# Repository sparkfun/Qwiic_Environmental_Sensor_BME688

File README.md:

SparkFun Environmental Sensor - BME688 (Qwiic)
========================================

[*SparkFun Environmental Sensor - BME688 (Qwiic) (SEN-19096)*](https://www.sparkfun.com/products/19096)

The SparkFun Environmental Sensor - BME688 (Qwiic) is a breakout board that combines a gas scanning sensor with temperature, humidity, and barometric pressure sensing for a complete environmental sensor in a single package. The gas sensor on the BME688 can detect a wide variety of volatile organic compounds (VOCs), volatile sulfur compounds (VSCs), and other gases such as carbon monoxide and hydrogen in the part per billion (ppb) range. Combine that with precise temperature, humidity, and barometric pressure and the BME688 can work as a completely standalone environmental sensor all in a 1in. x 1in. breakout!

The sensor communicates via either I2C or SPI. We've broken out the I2C pins to our Qwiic system so no soldering is required to connect it to the rest of your system but if you would prefer, both the I2C and SPI pins are also broken out to standard 0.1in.-spaced pins.

**Note:** While this sensor can be used with the BME AI-Studio and BSEC2 Arduino library; it is recommended for the AI functionality, users purchase the BME688 Evaluation Board (Coming Soon) for ease of use.

<p><div class="alert alert-warning"><b>Important:</b> In order to avoid contamination of its gas scanning capabilities, DO NOT touch the metallic casing of the BME688 sensor. Please, handle with care.</div></p>

_The SparkFun [Qwiic connect system](https://www.sparkfun.com/qwiic) is an ecosystem of I2C sensors, actuators, shields and cables that make prototyping faster and less prone to error. All Qwiic-enabled boards use a common 1mm pitch, 4-pin JST connector. This reduces the amount of required PCB space, and polarized connections mean you can’t hook it up wrong._

Repository Contents
-------------------

* **/Test Sketches** - Engineer's Arduino example code
* **/Hardware** - Eagle design files (.brd, .sch)
* **/Hardware/Production** - Production panel files (.brd)

Documentation
--------------

* **[Datasheet](https://www.bosch-sensortec.com/media/boschsensortec/downloads/datasheets/bst-bme688-ds000.pdf)** - BME688 Datasheet
* **[Hookup Guide](https://learn.sparkfun.com/tutorials/1168)** - SparkFun Environmental Sensor Breakout - BME68x (Qwiic) Hookup Guide
* **Arduino Libraries:**
    * **[BME680 Arduino Library](https://github.com/SV-Zanshin/BME680)** - Arduino Library used in Hookup Guide
    * **[BME68x Arduino Library](https://github.com/BoschSensortec/Bosch-BME68x-Library)** - Bosch's Arduino Library for BME68x Sensors
    * **[BSEC2 Arduino Library](https://github.com/BoschSensortec/Bosch-BSEC2-Library)** - Bosch's Arduino Library for BME AI-Studio
* **BME AI Studio:**
    * **BME AI-Studio (Mac/Windows)** *(Download from [Bosch software page](https://www.bosch-sensortec.com/software-tools/software/bme688-software/))*
    * **[BME AI-Studio Manual](https://www.bosch-sensortec.com/media/boschsensortec/downloads/application_notes_1/bst-bme688-an001.pdf)** - User Manual for BME AI-Studio

Product Versions
----------------
* [SEN-19096](https://www.sparkfun.com/products/19096) -  initial release

License Information
-------------------

This product is _**open source**_! 

Please review the LICENSE.md file for license information. 

If you have any questions or concerns on licensing, please contact technical support on our [SparkFun forums](https://forum.sparkfun.com/viewforum.php?f=152).

Distributed as-is; no warranty is given.

- Your friends at SparkFun.

_<COLLABORATION CREDIT>_

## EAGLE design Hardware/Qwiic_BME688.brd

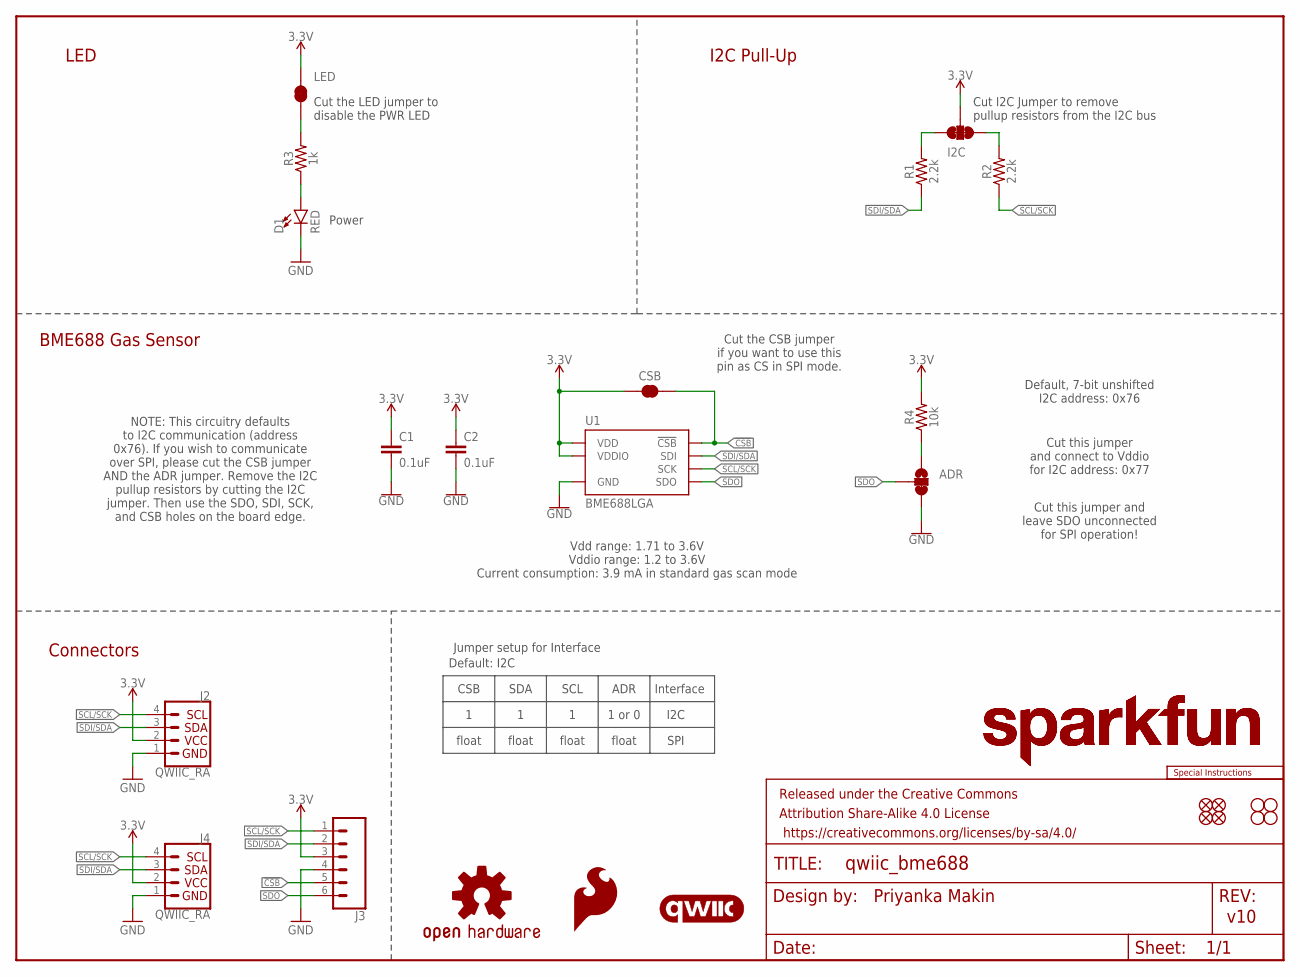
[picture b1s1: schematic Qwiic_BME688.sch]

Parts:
ADR: JUMPER-SMT_3_1-NC_TRACE_SILK; SMT-JUMPER_3_1-NC_TRACE_SILK
C1, C2: 0.1uF; 0603
CSB: JUMPER-SMT_2_NC_TRACE_SILK; SMT-JUMPER_2_NC_TRACE_SILK
D1: RED; LED-0603
FRAME1: FRAME-LETTER; CREATIVE_COMMONS
I2C: JUMPER-SMT_3_2-NC_TRACE_SILK; SMT-JUMPER_3_2-NC_TRACE_SILK
J2, J4: QWIIC_RA; JST04_1MM_RA
J3: CONN_06NO_SILK_NO_POP; 1X06_NO_SILK
JP1, JP2, JP5, JP6: FIDUCIALUFIDUCIAL; FIDUCIAL-MICRO
JP3, JP4, JP7, JP8: STAND-OFF
LED: JUMPER-SMT_2_NC_TRACE_SILK; SMT-JUMPER_2_NC_TRACE_SILK
LOGO1: SPECIAL_INSTRUCTIONS-ORDERING; ORDERING_INSTRUCTIONS
LOGO2: QWIIC_LOGO_5MM; QWIIC_5MM
LOGO3, LOGO6: SFE_LOGO_NAME.1_INCH; SFE_LOGO_NAME_.1
LOGO4: SFE_LOGO_FLAME.1_INCH; SFE_LOGO_FLAME_.1
LOGO5: OSHW-LOGOS; OSHW-LOGO-S
R1, R2: 2.2k; 0603
R3: 1k; 0603
R4: 10k; 0603
U1: BME688LGA; LGA_8PIN

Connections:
3.3V: C1.1, C2.1, CSB.1, I2C.2, J2.2, J3.3, J4.2, LED.2, R4.2, U1.6 (VDDIO), U1.8 (VDD)
!CSB!: CSB.2, J3.5, U1.2 (!CSB!)
GND: ADR.3, C1.2, C2.2, D1.C, J2.1, J3.4, J4.1, U1.1 (GND), U1.7 (GND)
unnamed: LED.1, R3.2
unnamed: I2C.3, R1.2
unnamed: D1.A, R3.1
unnamed: I2C.1, R2.2
unnamed: ADR.1, R4.1
SCL/SCK: J2.4, J3.1, J4.4, R2.1, U1.4 (SCK)
SDI/SDA: J2.3, J3.2, J4.3, R1.1, U1.3 (SDI)
SDO: ADR.2, J3.6, U1.5 (SDO)

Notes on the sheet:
v10
Default, 7-bit unshifted I2C address: 0x76
Power
I2C Pull-Up
BME688 Gas Sensor
Connectors
Cut the LED jumper to disable the PWR LED
Cut I2C Jumper to remove pullup resistors from the I2C bus
LED
Priyanka Makin
Vdd range: 1.71 to 3.6V Vddio range: 1.2 to 3.6V Current consumption: 3.9 mA in standard gas scan mode
Cut this jumper and connect to Vddio for I2C address: 0x77
Cut this jumper and leave SDO unconnected for SPI operation!
Cut the CSB jumper if you want to use this pin as CS in SPI mode.
NOTE: This circuitry defaults to I2C communication (address 0x76). If you wish to communicate over SPI, please cut the CSB jumper AND the ADR jumper. Remove the I2C pullup resistors by cutting the I2C jumper. Then use the SDO, SDI, SCK, and CSB holes on the board edge.
SCL
CSB
ADR
1 or 0
float
Interface
I2C
SPI
SDA
Jumper setup for Interface
Default: I2C

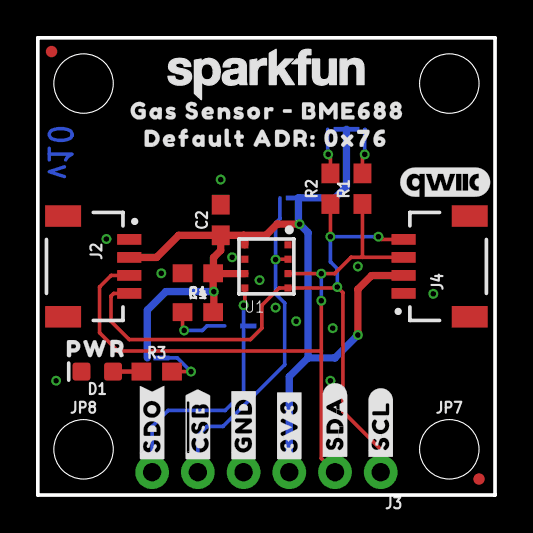
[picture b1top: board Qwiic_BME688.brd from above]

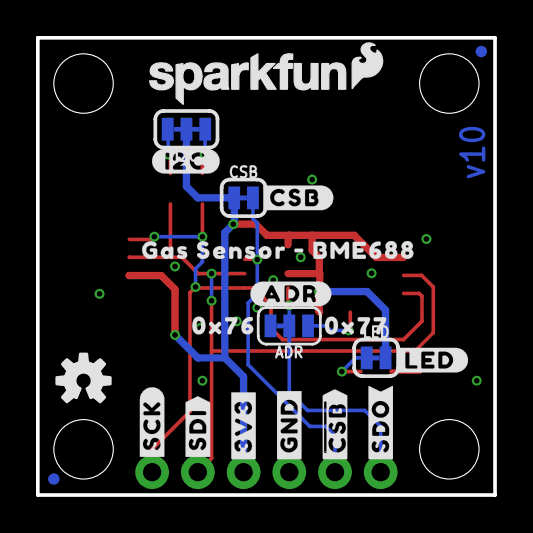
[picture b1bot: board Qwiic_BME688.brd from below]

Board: 2 copper layers, 25.4 x 25.4 mm, 52 parts (22 on the bottom side), 11 nets.

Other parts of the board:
U$1, U$33: #GND#0
U$2, U$16: #SDO#0
U$3: #CSB#0
U$5: PWR0
U$6: #I2C#0
U$7, U$10: GAS_SENSOR_#_BME6880
U$8: #LED#0
U$9: 0X760
U$11: #ADR#0
U$12: DEFAULT_ADR#_0X760
U$13: 0X770
U$14, U$15: #3V3#0
U$19: #SDI#0
U$20: #SCK#0
U$21, U$22: ##CSB##0
U$35: #SDA#0
U$36: #SCL#0

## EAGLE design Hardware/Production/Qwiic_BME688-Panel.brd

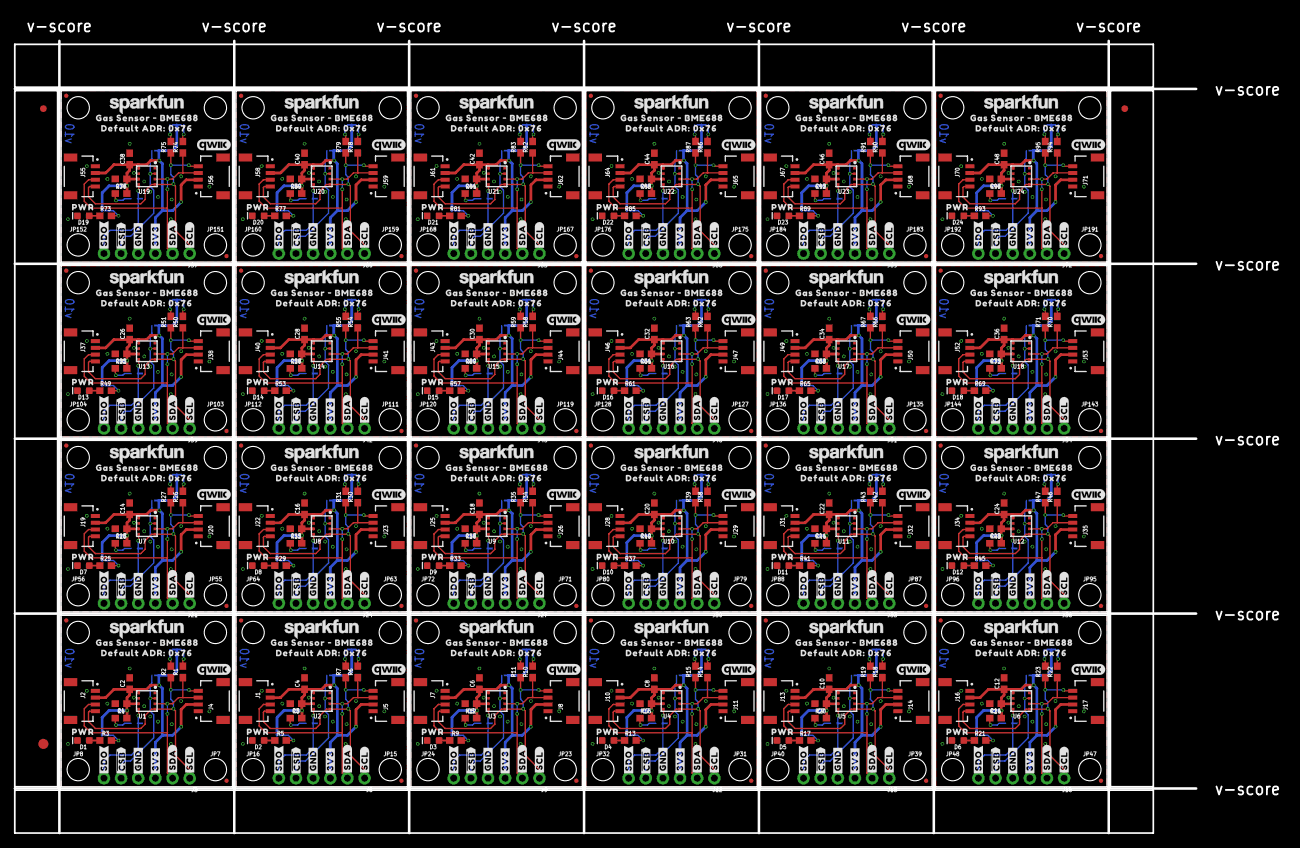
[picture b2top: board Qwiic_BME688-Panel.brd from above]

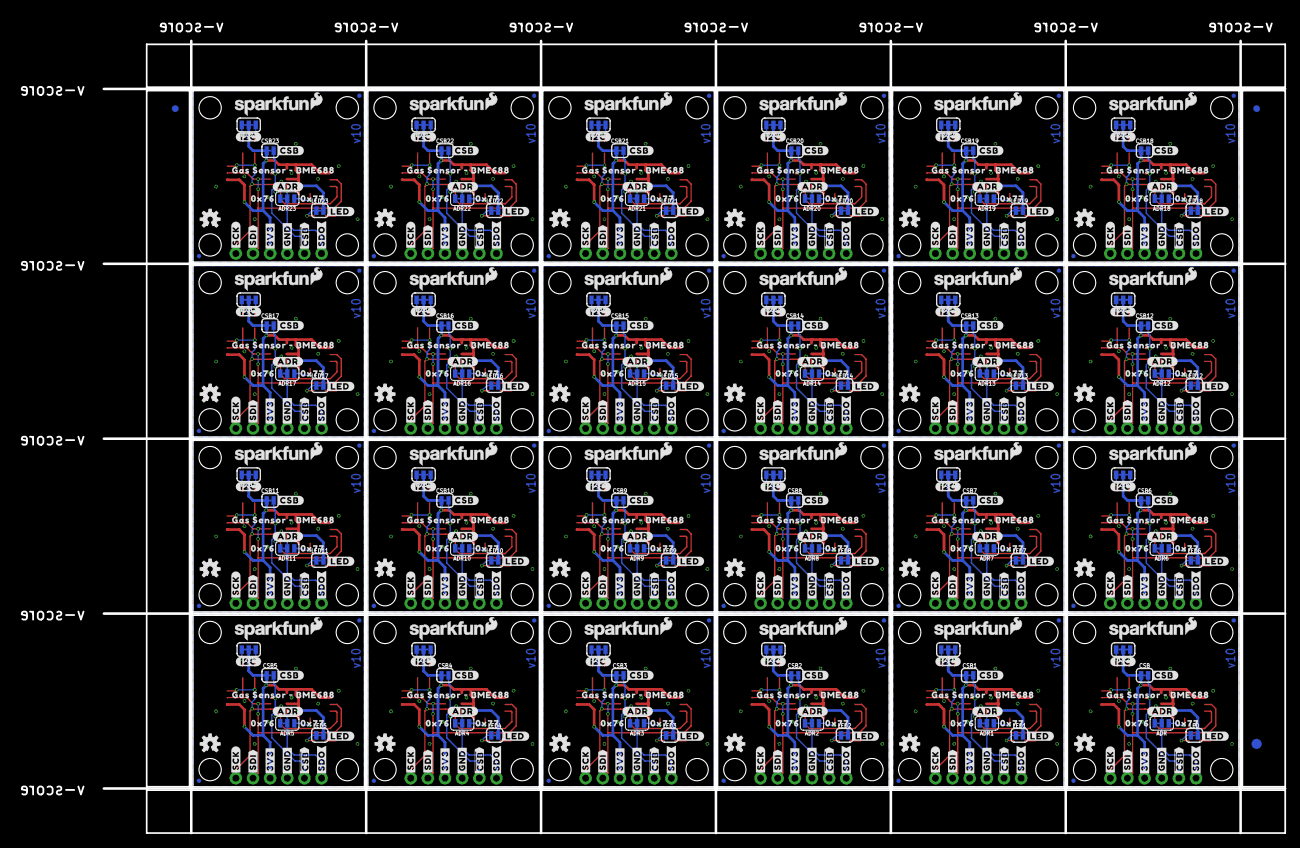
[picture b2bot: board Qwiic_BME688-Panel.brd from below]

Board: 2 copper layers, 188.2 x 121.2 mm, 1206 parts (531 on the bottom side), 264 nets.

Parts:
ADR, ADR1, ADR2, ADR3, ADR4, ADR5, ADR6, ADR7, ADR8, ADR9, ADR10, ADR11, ADR12, ADR13, ADR14, ADR15, ADR16, ADR17, ADR18, ADR19, ADR20, ADR21, ADR22, ADR23: JUMPER-SMT_3_1-NC_TRACE_SILK; SMT-JUMPER_3_1-NC_TRACE_SILK
C1, C2, C3, C4, C5, C6, C7, C8, C9, C10, C11, C12, C13, C14, C15, C16, C17, C18, C19, C20, C21, C22, C23, C24, C25, C26, C27, C28, C29, C30, C31, C32, C33, C34, C35, C36, C37, C38, C39, C40, C41, C42, C43, C44, C45, C46, C47, C48: 0.1uF; 0603
CSB, CSB1, CSB2, CSB3, CSB4, CSB5, CSB6, CSB7, CSB8, CSB9, CSB10, CSB11, CSB12, CSB13, CSB14, CSB15, CSB16, CSB17, CSB18, CSB19, CSB20, CSB21, CSB22, CSB23: JUMPER-SMT_2_NC_TRACE_SILK; SMT-JUMPER_2_NC_TRACE_SILK
D1, D2, D3, D4, D5, D6, D7, D8, D9, D10, D11, D12, D13, D14, D15, D16, D17, D18, D19, D20, D21, D22, D23, D24: RED; LED-0603
E$1, E$2, E$3, E$4: FIDUCIAL-1X2
E$5, E$6: FIDUCIAL-1.5X3
I2C, I2C1, I2C2, I2C3, I2C4, I2C5, I2C6, I2C7, I2C8, I2C9, I2C10, I2C11, I2C12, I2C13, I2C14, I2C15, I2C16, I2C17, I2C18, I2C19, I2C20, I2C21, I2C22, I2C23: JUMPER-SMT_3_2-NC_TRACE_SILK; SMT-JUMPER_3_2-NC_TRACE_SILK
J1, J2, J4, J5, J7, J8, J10, J11, J13, J14, J16, J17, J19, J20, J22, J23, J25, J26, J28, J29, J31, J32, J34, J35, J37, J38, J40, J41, J43, J44, J46, J47, J49, J50, J52, J53, J55, J56, J58, J59, J61, J62, J64, J65, J67, J68, J70, J71: QWIIC_RA; JST04_1MM_RA
J3, J6, J9, J12, J15, J18, J21, J24, J27, J30, J33, J36, J39, J42, J45, J48, J51, J54, J57, J60, J63, J66, J69, J72: 1X06_NO_SILK
JP1, JP2, JP5, JP6, JP11, JP12, JP13, JP14, JP19, JP20, JP21, JP22, JP27, JP28, JP29, JP30, JP35, JP36, JP37, JP38, JP43, JP44, JP45, JP46, JP51, JP52, JP53, JP54, JP59, JP60, JP61, JP62, JP67, JP68, JP69, JP70, JP75, JP76, JP77, JP78, JP83, JP84, JP85, JP86, JP91, JP92, JP93, JP94, JP99, JP100, JP101, JP102, JP107, JP108, JP109, JP110, JP115, JP116, JP117, JP118, JP123, JP124, JP125, JP126, JP131, JP132, JP133, JP134, JP139, JP140, JP141, JP142, JP147, JP148, JP149, JP150, JP155, JP156, JP157, JP158, JP163, JP164, JP165, JP166, JP171, JP172, JP173, JP174, JP179, JP180, JP181, JP182, JP187, JP188, JP189, JP190: FIDUCIALUFIDUCIAL; FIDUCIAL-MICRO
JP3, JP4, JP7, JP8, JP9, JP10, JP15, JP16, JP17, JP18, JP23, JP24, JP25, JP26, JP31, JP32, JP33, JP34, JP39, JP40, JP41, JP42, JP47, JP48, JP49, JP50, JP55, JP56, JP57, JP58, JP63, JP64, JP65, JP66, JP71, JP72, JP73, JP74, JP79, JP80, JP81, JP82, JP87, JP88, JP89, JP90, JP95, JP96, JP97, JP98, JP103, JP104, JP105, JP106, JP111, JP112, JP113, JP114, JP119, JP120, JP121, JP122, JP127, JP128, JP129, JP130, JP135, JP136, JP137, JP138, JP143, JP144, JP145, JP146, JP151, JP152, JP153, JP154, JP159, JP160, JP161, JP162, JP167, JP168, JP169, JP170, JP175, JP176, JP177, JP178, JP183, JP184, JP185, JP186, JP191, JP192: STAND-OFF
LED, LED1, LED2, LED3, LED4, LED5, LED6, LED7, LED8, LED9, LED10, LED11, LED12, LED13, LED14, LED15, LED16, LED17, LED18, LED19, LED20, LED21, LED22, LED23: JUMPER-SMT_2_NC_TRACE_SILK; SMT-JUMPER_2_NC_TRACE_SILK
LOGO1, LOGO5, LOGO11, LOGO16, LOGO21, LOGO26, LOGO31, LOGO36, LOGO41, LOGO46, LOGO51, LOGO56, LOGO61, LOGO66, LOGO71, LOGO76, LOGO81, LOGO86, LOGO91, LOGO96, LOGO101, LOGO106, LOGO111, LOGO116: OSHW-LOGOS; OSHW-LOGO-S
LOGO2, LOGO7, LOGO12, LOGO17, LOGO22, LOGO27, LOGO32, LOGO37, LOGO42, LOGO47, LOGO52, LOGO57, LOGO62, LOGO67, LOGO72, LOGO77, LOGO82, LOGO87, LOGO92, LOGO97, LOGO102, LOGO107, LOGO112, LOGO117: QWIIC_LOGO_5MM; QWIIC_5MM
LOGO3, LOGO6, LOGO8, LOGO10, LOGO13, LOGO15, LOGO18, LOGO20, LOGO23, LOGO25, LOGO28, LOGO30, LOGO33, LOGO35, LOGO38, LOGO40, LOGO43, LOGO45, LOGO48, LOGO50, LOGO53, LOGO55, LOGO58, LOGO60, LOGO63, LOGO65, LOGO68, LOGO70, LOGO73, LOGO75, LOGO78, LOGO80, LOGO83, LOGO85, LOGO88, LOGO90, LOGO93, LOGO95, LOGO98, LOGO100, LOGO103, LOGO105, LOGO108, LOGO110, LOGO113, LOGO115, LOGO118, LOGO120: SFE_LOGO_NAME.1_INCH; SFE_LOGO_NAME_.1
LOGO4, LOGO9, LOGO14, LOGO19, LOGO24, LOGO29, LOGO34, LOGO39, LOGO44, LOGO49, LOGO54, LOGO59, LOGO64, LOGO69, LOGO74, LOGO79, LOGO84, LOGO89, LOGO94, LOGO99, LOGO104, LOGO109, LOGO114, LOGO119: SFE_LOGO_FLAME.1_INCH; SFE_LOGO_FLAME_.1
R1, R2, R6, R7, R10, R11, R14, R15, R18, R19, R22, R23, R26, R27, R30, R31, R34, R35, R38, R39, R42, R43, R46, R47, R50, R51, R54, R55, R58, R59, R62, R63, R66, R67, R70, R71, R74, R75, R78, R79, R82, R83, R86, R87, R90, R91, R94, R95: 2.2k; 0603
R3, R5, R9, R13, R17, R21, R25, R29, R33, R37, R41, R45, R49, R53, R57, R61, R65, R69, R73, R77, R81, R85, R89, R93: 1k; 0603
R4, R8, R12, R16, R20, R24, R28, R32, R36, R40, R44, R48, R52, R56, R60, R64, R68, R72, R76, R80, R84, R88, R92, R96: 10k; 0603
U1, U2, U3, U4, U5, U6, U7, U8, U9, U10, U11, U12, U13, U14, U15, U16, U17, U18, U19, U20, U21, U22, U23, U24: BME688LGA; LGA_8PIN
U$1, U$4, U$23, U$33, U$45, U$48, U$67, U$70, U$89, U$92, U$111, U$114, U$133, U$136, U$155, U$158, U$177, U$180, U$199, U$202, U$221, U$224, U$243, U$246, U$265, U$268, U$287, U$290, U$309, U$312, U$331, U$334, U$353, U$356, U$375, U$378, U$397, U$400, U$419, U$422, U$441, U$444, U$463, U$466, U$485, U$488, U$507, U$510: #GND#0
U$2, U$16, U$38, U$39, U$60, U$61, U$82, U$83, U$104, U$105, U$126, U$127, U$148, U$149, U$170, U$171, U$192, U$193, U$214, U$215, U$236, U$237, U$258, U$259, U$280, U$281, U$302, U$303, U$324, U$325, U$346, U$347, U$368, U$369, U$390, U$391, U$412, U$413, U$434, U$435, U$456, U$457, U$478, U$479, U$500, U$501, U$522, U$523: #SDO#0
U$3, U$42, U$64, U$86, U$108, U$130, U$152, U$174, U$196, U$218, U$240, U$262, U$284, U$306, U$328, U$350, U$372, U$394, U$416, U$438, U$460, U$482, U$504, U$526: #CSB#0
U$5, U$24, U$49, U$71, U$93, U$115, U$137, U$159, U$181, U$203, U$225, U$247, U$269, U$291, U$313, U$335, U$357, U$379, U$401, U$423, U$445, U$467, U$489, U$511: PWR0
U$6, U$29, U$54, U$76, U$98, U$120, U$142, U$164, U$186, U$208, U$230, U$252, U$274, U$296, U$318, U$340, U$362, U$384, U$406, U$428, U$450, U$472, U$494, U$516: #I2C#0
U$7, U$10, U$25, U$27, U$50, U$52, U$72, U$74, U$94, U$96, U$116, U$118, U$138, U$140, U$160, U$162, U$182, U$184, U$204, U$206, U$226, U$228, U$248, U$250, U$270, U$272, U$292, U$294, U$314, U$316, U$336, U$338, U$358, U$360, U$380, U$382, U$402, U$404, U$424, U$426, U$446, U$448, U$468, U$470, U$490, U$492, U$512, U$514: GAS_SENSOR_#_BME6880
U$8, U$28, U$53, U$75, U$97, U$119, U$141, U$163, U$185, U$207, U$229, U$251, U$273, U$295, U$317, U$339, U$361, U$383, U$405, U$427, U$449, U$471, U$493, U$515: #LED#0
U$9, U$31, U$56, U$78, U$100, U$122, U$144, U$166, U$188, U$210, U$232, U$254, U$276, U$298, U$320, U$342, U$364, U$386, U$408, U$430, U$452, U$474, U$496, U$518: 0X760
U$11, U$26, U$51, U$73, U$95, U$117, U$139, U$161, U$183, U$205, U$227, U$249, U$271, U$293, U$315, U$337, U$359, U$381, U$403, U$425, U$447, U$469, U$491, U$513: #ADR#0
U$12, U$30, U$55, U$77, U$99, U$121, U$143, U$165, U$187, U$209, U$231, U$253, U$275, U$297, U$319, U$341, U$363, U$385, U$407, U$429, U$451, U$473, U$495, U$517: DEFAULT_ADR#_0X760
U$13, U$32, U$57, U$79, U$101, U$123, U$145, U$167, U$189, U$211, U$233, U$255, U$277, U$299, U$321, U$343, U$365, U$387, U$409, U$431, U$453, U$475, U$497, U$519: 0X770
U$14, U$15, U$34, U$37, U$58, U$59, U$80, U$81, U$102, U$103, U$124, U$125, U$146, U$147, U$168, U$169, U$190, U$191, U$212, U$213, U$234, U$235, U$256, U$257, U$278, U$279, U$300, U$301, U$322, U$323, U$344, U$345, U$366, U$367, U$388, U$389, U$410, U$411, U$432, U$433, U$454, U$455, U$476, U$477, U$498, U$499, U$520, U$521: #3V3#0
U$17, U$35, U$46, U$68, U$90, U$112, U$134, U$156, U$178, U$200, U$222, U$244, U$266, U$288, U$310, U$332, U$354, U$376, U$398, U$420, U$442, U$464, U$486, U$508: #SDA#0
U$18, U$36, U$47, U$69, U$91, U$113, U$135, U$157, U$179, U$201, U$223, U$245, U$267, U$289, U$311, U$333, U$355, U$377, U$399, U$421, U$443, U$465, U$487, U$509: #SCL#0
U$19, U$40, U$62, U$84, U$106, U$128, U$150, U$172, U$194, U$216, U$238, U$260, U$282, U$304, U$326, U$348, U$370, U$392, U$414, U$436, U$458, U$480, U$502, U$524: #SDI#0
U$20, U$41, U$63, U$85, U$107, U$129, U$151, U$173, U$195, U$217, U$239, U$261, U$283, U$305, U$327, U$349, U$371, U$393, U$415, U$437, U$459, U$481, U$503, U$525: #SCK#0
U$21, U$22, U$43, U$44, U$65, U$66, U$87, U$88, U$109, U$110, U$131, U$132, U$153, U$154, U$175, U$176, U$197, U$198, U$219, U$220, U$241, U$242, U$263, U$264, U$285, U$286, U$307, U$308, U$329, U$330, U$351, U$352, U$373, U$374, U$395, U$396, U$417, U$418, U$439, U$440, U$461, U$462, U$483, U$484, U$505, U$506, U$527, U$528: ##CSB##0

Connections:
3.3V: C1.1, C2.1, CSB.1, I2C.2, J2.2, J3.3, J4.2, LED.2, R4.2, U1.6, U1.8
3.3V1: C3.1, C4.1, CSB1.1, I2C1.2, J1.2, J5.2, J6.3, LED1.2, R8.2, U2.6, U2.8
3.3V2: C5.1, C6.1, CSB2.1, I2C2.2, J7.2, J8.2, J9.3, LED2.2, R12.2, U3.6, U3.8
3.3V3: C7.1, C8.1, CSB3.1, I2C3.2, J10.2, J11.2, J12.3, LED3.2, R16.2, U4.6, U4.8
3.3V4: C9.1, C10.1, CSB4.1, I2C4.2, J13.2, J14.2, J15.3, LED4.2, R20.2, U5.6, U5.8
3.3V5: C11.1, C12.1, CSB5.1, I2C5.2, J16.2, J17.2, J18.3, LED5.2, R24.2, U6.6, U6.8
3.3V6: C13.1, C14.1, CSB6.1, I2C6.2, J19.2, J20.2, J21.3, LED6.2, R28.2, U7.6, U7.8
3.3V7: C15.1, C16.1, CSB7.1, I2C7.2, J22.2, J23.2, J24.3, LED7.2, R32.2, U8.6, U8.8
3.3V8: C17.1, C18.1, CSB8.1, I2C8.2, J25.2, J26.2, J27.3, LED8.2, R36.2, U9.6, U9.8
3.3V9: C19.1, C20.1, CSB9.1, I2C9.2, J28.2, J29.2, J30.3, LED9.2, R40.2, U10.6, U10.8
3.3V10: C21.1, C22.1, CSB10.1, I2C10.2, J31.2, J32.2, J33.3, LED10.2, R44.2, U11.6, U11.8
3.3V11: C23.1, C24.1, CSB11.1, I2C11.2, J34.2, J35.2, J36.3, LED11.2, R48.2, U12.6, U12.8
3.3V12: C25.1, C26.1, CSB12.1, I2C12.2, J37.2, J38.2, J39.3, LED12.2, R52.2, U13.6, U13.8
3.3V13: C27.1, C28.1, CSB13.1, I2C13.2, J40.2, J41.2, J42.3, LED13.2, R56.2, U14.6, U14.8
3.3V14: C29.1, C30.1, CSB14.1, I2C14.2, J43.2, J44.2, J45.3, LED14.2, R60.2, U15.6, U15.8
3.3V15: C31.1, C32.1, CSB15.1, I2C15.2, J46.2, J47.2, J48.3, LED15.2, R64.2, U16.6, U16.8
3.3V16: C33.1, C34.1, CSB16.1, I2C16.2, J49.2, J50.2, J51.3, LED16.2, R68.2, U17.6, U17.8
3.3V17: C35.1, C36.1, CSB17.1, I2C17.2, J52.2, J53.2, J54.3, LED17.2, R72.2, U18.6, U18.8
3.3V18: C37.1, C38.1, CSB18.1, I2C18.2, J55.2, J56.2, J57.3, LED18.2, R76.2, U19.6, U19.8
3.3V19: C39.1, C40.1, CSB19.1, I2C19.2, J58.2, J59.2, J60.3, LED19.2, R80.2, U20.6, U20.8
3.3V20: C41.1, C42.1, CSB20.1, I2C20.2, J61.2, J62.2, J63.3, LED20.2, R84.2, U21.6, U21.8
3.3V21: C43.1, C44.1, CSB21.1, I2C21.2, J64.2, J65.2, J66.3, LED21.2, R88.2, U22.6, U22.8
3.3V22: C45.1, C46.1, CSB22.1, I2C22.2, J67.2, J68.2, J69.3, LED22.2, R92.2, U23.6, U23.8
3.3V23: C47.1, C48.1, CSB23.1, I2C23.2, J70.2, J71.2, J72.3, LED23.2, R96.2, U24.6, U24.8
!CSB!: CSB.2, J3.5, U1.2
!CSB!1: CSB1.2, J6.5, U2.2
!CSB!2: CSB2.2, J9.5, U3.2
!CSB!3: CSB3.2, J12.5, U4.2
!CSB!4: CSB4.2, J15.5, U5.2
!CSB!5: CSB5.2, J18.5, U6.2
!CSB!6: CSB6.2, J21.5, U7.2
!CSB!7: CSB7.2, J24.5, U8.2
!CSB!8: CSB8.2, J27.5, U9.2
!CSB!9: CSB9.2, J30.5, U10.2
!CSB!10: CSB10.2, J33.5, U11.2
!CSB!11: CSB11.2, J36.5, U12.2
!CSB!12: CSB12.2, J39.5, U13.2
!CSB!13: CSB13.2, J42.5, U14.2
!CSB!14: CSB14.2, J45.5, U15.2
!CSB!15: CSB15.2, J48.5, U16.2
!CSB!16: CSB16.2, J51.5, U17.2
!CSB!17: CSB17.2, J54.5, U18.2
!CSB!18: CSB18.2, J57.5, U19.2
!CSB!19: CSB19.2, J60.5, U20.2
!CSB!20: CSB20.2, J63.5, U21.2
!CSB!21: CSB21.2, J66.5, U22.2
!CSB!22: CSB22.2, J69.5, U23.2
!CSB!23: CSB23.2, J72.5, U24.2
GND: ADR.3, C1.2, C2.2, D1.C, J2.1, J3.4, J4.1, U1.1, U1.7
GND1: ADR1.3, C3.2, C4.2, D2.C, J1.1, J5.1, J6.4, U2.1, U2.7
GND2: ADR2.3, C5.2, C6.2, D3.C, J7.1, J8.1, J9.4, U3.1, U3.7
GND3: ADR3.3, C7.2, C8.2, D4.C, J10.1, J11.1, J12.4, U4.1, U4.7
GND4: ADR4.3, C9.2, C10.2, D5.C, J13.1, J14.1, J15.4, U5.1, U5.7
GND5: ADR5.3, C11.2, C12.2, D6.C, J16.1, J17.1, J18.4, U6.1, U6.7
GND6: ADR6.3, C13.2, C14.2, D7.C, J19.1, J20.1, J21.4, U7.1, U7.7
GND7: ADR7.3, C15.2, C16.2, D8.C, J22.1, J23.1, J24.4, U8.1, U8.7
GND8: ADR8.3, C17.2, C18.2, D9.C, J25.1, J26.1, J27.4, U9.1, U9.7
GND9: ADR9.3, C19.2, C20.2, D10.C, J28.1, J29.1, J30.4, U10.1, U10.7
GND10: ADR10.3, C21.2, C22.2, D11.C, J31.1, J32.1, J33.4, U11.1, U11.7
GND11: ADR11.3, C23.2, C24.2, D12.C, J34.1, J35.1, J36.4, U12.1, U12.7
GND12: ADR12.3, C25.2, C26.2, D13.C, J37.1, J38.1, J39.4, U13.1, U13.7
GND13: ADR13.3, C27.2, C28.2, D14.C, J40.1, J41.1, J42.4, U14.1, U14.7
GND14: ADR14.3, C29.2, C30.2, D15.C, J43.1, J44.1, J45.4, U15.1, U15.7
GND15: ADR15.3, C31.2, C32.2, D16.C, J46.1, J47.1, J48.4, U16.1, U16.7
GND16: ADR16.3, C33.2, C34.2, D17.C, J49.1, J50.1, J51.4, U17.1, U17.7
GND17: ADR17.3, C35.2, C36.2, D18.C, J52.1, J53.1, J54.4, U18.1, U18.7
GND18: ADR18.3, C37.2, C38.2, D19.C, J55.1, J56.1, J57.4, U19.1, U19.7
GND19: ADR19.3, C39.2, C40.2, D20.C, J58.1, J59.1, J60.4, U20.1, U20.7
GND20: ADR20.3, C41.2, C42.2, D21.C, J61.1, J62.1, J63.4, U21.1, U21.7
GND21: ADR21.3, C43.2, C44.2, D22.C, J64.1, J65.1, J66.4, U22.1, U22.7
GND22: ADR22.3, C45.2, C46.2, D23.C, J67.1, J68.1, J69.4, U23.1, U23.7
GND23: ADR23.3, C47.2, C48.2, D24.C, J70.1, J71.1, J72.4, U24.1, U24.7
unnamed: LED.1, R3.2
unnamed: I2C.3, R1.2
unnamed: D1.A, R3.1
unnamed: I2C.1, R2.2
unnamed: ADR.1, R4.1
unnamed: D2.A, R5.1
unnamed: LED1.1, R5.2
unnamed: I2C1.3, R6.2
unnamed: I2C1.1, R7.2
unnamed: ADR1.1, R8.1
unnamed: D3.A, R9.1
unnamed: LED2.1, R9.2
unnamed: I2C2.3, R10.2
unnamed: I2C2.1, R11.2
unnamed: ADR2.1, R12.1
unnamed: D4.A, R13.1
unnamed: LED3.1, R13.2
unnamed: I2C3.3, R14.2
unnamed: I2C3.1, R15.2
unnamed: ADR3.1, R16.1
unnamed: D5.A, R17.1
unnamed: LED4.1, R17.2
unnamed: I2C4.3, R18.2
unnamed: I2C4.1, R19.2
unnamed: ADR4.1, R20.1
unnamed: D6.A, R21.1
unnamed: LED5.1, R21.2
unnamed: I2C5.3, R22.2
unnamed: I2C5.1, R23.2
unnamed: ADR5.1, R24.1
unnamed: D7.A, R25.1
unnamed: LED6.1, R25.2
unnamed: I2C6.3, R26.2
unnamed: I2C6.1, R27.2
unnamed: ADR6.1, R28.1
unnamed: D8.A, R29.1
unnamed: LED7.1, R29.2
unnamed: I2C7.3, R30.2
unnamed: I2C7.1, R31.2
unnamed: ADR7.1, R32.1
unnamed: D9.A, R33.1
unnamed: LED8.1, R33.2
unnamed: I2C8.3, R34.2
unnamed: I2C8.1, R35.2
unnamed: ADR8.1, R36.1
unnamed: D10.A, R37.1
unnamed: LED9.1, R37.2
unnamed: I2C9.3, R38.2
unnamed: I2C9.1, R39.2
unnamed: ADR9.1, R40.1
unnamed: D11.A, R41.1
unnamed: LED10.1, R41.2
unnamed: I2C10.3, R42.2
unnamed: I2C10.1, R43.2
unnamed: ADR10.1, R44.1
unnamed: D12.A, R45.1
unnamed: LED11.1, R45.2
unnamed: I2C11.3, R46.2
unnamed: I2C11.1, R47.2
unnamed: ADR11.1, R48.1
unnamed: D13.A, R49.1
unnamed: LED12.1, R49.2
unnamed: I2C12.3, R50.2
unnamed: I2C12.1, R51.2
unnamed: ADR12.1, R52.1
unnamed: D14.A, R53.1
unnamed: LED13.1, R53.2
unnamed: I2C13.3, R54.2
unnamed: I2C13.1, R55.2
unnamed: ADR13.1, R56.1
unnamed: D15.A, R57.1
unnamed: LED14.1, R57.2
unnamed: I2C14.3, R58.2
unnamed: I2C14.1, R59.2
unnamed: ADR14.1, R60.1
unnamed: D16.A, R61.1
unnamed: LED15.1, R61.2
unnamed: I2C15.3, R62.2
unnamed: I2C15.1, R63.2
unnamed: ADR15.1, R64.1
unnamed: D17.A, R65.1
unnamed: LED16.1, R65.2
unnamed: I2C16.3, R66.2
unnamed: I2C16.1, R67.2
unnamed: ADR16.1, R68.1
unnamed: D18.A, R69.1
unnamed: LED17.1, R69.2
unnamed: I2C17.3, R70.2
unnamed: I2C17.1, R71.2
unnamed: ADR17.1, R72.1
unnamed: D19.A, R73.1
unnamed: LED18.1, R73.2
unnamed: I2C18.3, R74.2
unnamed: I2C18.1, R75.2
unnamed: ADR18.1, R76.1
unnamed: D20.A, R77.1
unnamed: LED19.1, R77.2
unnamed: I2C19.3, R78.2
unnamed: I2C19.1, R79.2
unnamed: ADR19.1, R80.1
unnamed: D21.A, R81.1
unnamed: LED20.1, R81.2
unnamed: I2C20.3, R82.2
unnamed: I2C20.1, R83.2
unnamed: ADR20.1, R84.1
unnamed: D22.A, R85.1
unnamed: LED21.1, R85.2
unnamed: I2C21.3, R86.2
unnamed: I2C21.1, R87.2
unnamed: ADR21.1, R88.1
unnamed: D23.A, R89.1
unnamed: LED22.1, R89.2
unnamed: I2C22.3, R90.2
unnamed: I2C22.1, R91.2
unnamed: ADR22.1, R92.1
unnamed: D24.A, R93.1
unnamed: LED23.1, R93.2
unnamed: I2C23.3, R94.2
unnamed: I2C23.1, R95.2
unnamed: ADR23.1, R96.1
SCL/SCK: J2.4, J3.1, J4.4, R2.1, U1.4
SCL/SCK1: J1.4, J5.4, J6.1, R7.1, U2.4
SCL/SCK2: J7.4, J8.4, J9.1, R11.1, U3.4
SCL/SCK3: J10.4, J11.4, J12.1, R15.1, U4.4
SCL/SCK4: J13.4, J14.4, J15.1, R19.1, U5.4
SCL/SCK5: J16.4, J17.4, J18.1, R23.1, U6.4
SCL/SCK6: J19.4, J20.4, J21.1, R27.1, U7.4
SCL/SCK7: J22.4, J23.4, J24.1, R31.1, U8.4
SCL/SCK8: J25.4, J26.4, J27.1, R35.1, U9.4
SCL/SCK9: J28.4, J29.4, J30.1, R39.1, U10.4
SCL/SCK10: J31.4, J32.4, J33.1, R43.1, U11.4
SCL/SCK11: J34.4, J35.4, J36.1, R47.1, U12.4
SCL/SCK12: J37.4, J38.4, J39.1, R51.1, U13.4
SCL/SCK13: J40.4, J41.4, J42.1, R55.1, U14.4
SCL/SCK14: J43.4, J44.4, J45.1, R59.1, U15.4
SCL/SCK15: J46.4, J47.4, J48.1, R63.1, U16.4
SCL/SCK16: J49.4, J50.4, J51.1, R67.1, U17.4
SCL/SCK17: J52.4, J53.4, J54.1, R71.1, U18.4
SCL/SCK18: J55.4, J56.4, J57.1, R75.1, U19.4
SCL/SCK19: J58.4, J59.4, J60.1, R79.1, U20.4
SCL/SCK20: J61.4, J62.4, J63.1, R83.1, U21.4
SCL/SCK21: J64.4, J65.4, J66.1, R87.1, U22.4
SCL/SCK22: J67.4, J68.4, J69.1, R91.1, U23.4
SCL/SCK23: J70.4, J71.4, J72.1, R95.1, U24.4
SDA/PICO: J2.3, J3.2, J4.3, R1.1, U1.3
SDA/PICO1: J1.3, J5.3, J6.2, R6.1, U2.3
SDA/PICO2: J7.3, J8.3, J9.2, R10.1, U3.3
SDA/PICO3: J10.3, J11.3, J12.2, R14.1, U4.3
SDA/PICO4: J13.3, J14.3, J15.2, R18.1, U5.3
SDA/PICO5: J16.3, J17.3, J18.2, R22.1, U6.3
SDA/PICO6: J19.3, J20.3, J21.2, R26.1, U7.3
SDA/PICO7: J22.3, J23.3, J24.2, R30.1, U8.3
SDA/PICO8: J25.3, J26.3, J27.2, R34.1, U9.3
SDA/PICO9: J28.3, J29.3, J30.2, R38.1, U10.3
SDA/PICO10: J31.3, J32.3, J33.2, R42.1, U11.3
SDA/PICO11: J34.3, J35.3, J36.2, R46.1, U12.3
SDA/PICO12: J37.3, J38.3, J39.2, R50.1, U13.3
SDA/PICO13: J40.3, J41.3, J42.2, R54.1, U14.3
SDA/PICO14: J43.3, J44.3, J45.2, R58.1, U15.3
SDA/PICO15: J46.3, J47.3, J48.2, R62.1, U16.3
SDA/PICO16: J49.3, J50.3, J51.2, R66.1, U17.3
SDA/PICO17: J52.3, J53.3, J54.2, R70.1, U18.3
SDA/PICO18: J55.3, J56.3, J57.2, R74.1, U19.3
SDA/PICO19: J58.3, J59.3, J60.2, R78.1, U20.3
SDA/PICO20: J61.3, J62.3, J63.2, R82.1, U21.3
SDA/PICO21: J64.3, J65.3, J66.2, R86.1, U22.3
SDA/PICO22: J67.3, J68.3, J69.2, R90.1, U23.3
SDA/PICO23: J70.3, J71.3, J72.2, R94.1, U24.3
SDO/POCI: ADR.2, J3.6, U1.5
SDO/POCI1: ADR1.2, J6.6, U2.5
SDO/POCI2: ADR2.2, J9.6, U3.5
SDO/POCI3: ADR3.2, J12.6, U4.5
SDO/POCI4: ADR4.2, J15.6, U5.5
SDO/POCI5: ADR5.2, J18.6, U6.5
SDO/POCI6: ADR6.2, J21.6, U7.5
SDO/POCI7: ADR7.2, J24.6, U8.5
SDO/POCI8: ADR8.2, J27.6, U9.5
SDO/POCI9: ADR9.2, J30.6, U10.5
SDO/POCI10: ADR10.2, J33.6, U11.5
SDO/POCI11: ADR11.2, J36.6, U12.5
SDO/POCI12: ADR12.2, J39.6, U13.5
SDO/POCI13: ADR13.2, J42.6, U14.5
SDO/POCI14: ADR14.2, J45.6, U15.5
SDO/POCI15: ADR15.2, J48.6, U16.5
SDO/POCI16: ADR16.2, J51.6, U17.5
SDO/POCI17: ADR17.2, J54.6, U18.5
SDO/POCI18: ADR18.2, J57.6, U19.5
SDO/POCI19: ADR19.2, J60.6, U20.5
SDO/POCI20: ADR20.2, J63.6, U21.5
SDO/POCI21: ADR21.2, J66.6, U22.5
SDO/POCI22: ADR22.2, J69.6, U23.5
SDO/POCI23: ADR23.2, J72.6, U24.5

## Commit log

2021-12-14 Initial commit - add docs
2021-12-16 initial hardware commit
2021-12-16 Create BME688 eagle footprint and schematic symbol
2021-12-16 Schematic done
2021-12-16 Updating schematic
2021-12-17 Board routed
2021-12-17 Buzzard labels
2021-12-21 Design review updates
    Schematic:
    * Add headers for CSB and SDO
    * Add NC jumper between CSB and 3.3V
    * Add 10k resistor for 3-way jumper
    * Replace I2C pullups with 2.2kohms
    * Increase the size of fiducials
2021-12-21 Design review updates - buzzard labels
2021-12-21 Engineering checklist
2021-12-21 Double check
    Add note clarifying configuration to SPI mode.
2021-12-22 Update net names
2021-12-22 Generate gerbers
2022-02-11 Fixed formatting of examples
2022-02-11 Updates to hardware v02
2022-02-11 Run new CAM for v02
2022-02-11 Update version number
2022-02-15 Design review changes
    * Add table for jumper selection
    * Nudge board name silk (on bottom) to avoid vias
2022-02-15 Update the CSB label
2022-02-16 QC Double-check:
    * Add active low line to "CSB" net label in the schematic
    * Updated jumper selection table
2022-02-16 Run CAM and Panelize
2022-02-16 Update BME688 schematic symbol
    * CSB pin to !CSB!
2022-04-07 Rename PICO/POCI net labels to CIPO/COPI
2022-04-07 Rename PICO/POCI labels to SDO/SDI
2022-04-07 Change I2C jumper notes on schematic
2022-05-04 Update README.md
    Add product information
2022-05-05 File Cleanup
    Remove proto panel files

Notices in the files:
parts and their libraries:
SparkFun-Resistors: Licensing: Creative Commons ShareAlike 4.0 International - https://creativecommons.org/licenses/by-sa/4.0
SparkFun-Aesthetics: Released under the Creative Commons Attribution Share-Alike 4.0 License
SparkFun-Aesthetics: https://creativecommons.org/licenses/by-sa/4.0
